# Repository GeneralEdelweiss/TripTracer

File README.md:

# TripTracer – GPS Rally & Trip Computer

Privates Entwicklungsprojekt eines selbstgebauten GPS-Tripmasters, universell fuer Rallye, Touren und Fahrzeuge. Zentraler, portabler Entwicklungsstand inklusive KiCad-10-Schaltplan, Bibliotheken, STEP-Modellen, erstem Gehaeuse und experimenteller Firmware.

## Projektstand (Oktober 2026)

| Teil | Stand | Bemerkung |
| --- | --- | --- |
| Schaltplan | V0.3 | 69 Instanzen, 25 Footprinttypen; strukturell geprueft, ERC nicht ausgefuehrt |
| Leiterplatte | Offen | **Keine geroutete, freigegebene PCB-Datei** |
| Symbole/Footprints/3D | V0.3 | Projektlokal und zentrale Kopie, Geometrie und Modelle noch zu verifizieren |
| Gehaeuse | V0.1 | Front/Rueckdeckel, Kappe, Referenzgeometrie als STEP/STL; Passprobe offen |
| Firmware | V0.1 | Experimenteller ESP32-S3-Prototyp, noch nicht mit V0.3 abgeglichen |

## Verzeichnisse

- `hardware/kicad/`: originaler V0.3-Schaltplan, projektlokale Symbole, Footprints, STEP-Modelle, Bibliothekstabellen
- `hardware/pcb/`: spaeteres Layout, momentan nur Hinweis
- `symbols/`, `footprints/`, `3dmodels/`: aus V0.3 uebernommene zentrale Bibliothekskopien
- `catalog/`: V0.3-BOM, Pin-/Netztabellen, Strukturpruefberichte, Modellinventar
- `mechanics/prototype_v0.1/`: mechanischer Prototyp (STEP/STL)
- `firmware/prototype_v0.1/`: PlatformIO-Prototyp
- `docs/HARDWARE_REQUIREMENTS.md`: zentrale Hardware-Anforderungen, Entscheidungen und offene Fragen fuer die naechste Revision
- `docs/`: Architektur, Datenblatt-URLs, Preview und offene Punkte
- `tools/legacy_generation/`: reproduzierbare Skripte der V0.3, **nicht ungefragt erneut ausfuehren**, da UUIDs neu vergeben werden koennen
- `integration/`: Bibliothekseinbindung auf weiteren Rechnern
- `releases/`: erst nach Freigabe fuellen

## Oeffnen

1. Repository klonen, KiCad 10 installieren.
2. `hardware/kicad/Tripmaster_V0_3.kicad_pro` oeffnen.
3. Bibliothekstabellen und 3D-Modelle aus demselben Ordner unveraendert belassen.
4. ERC in KiCad ausfuehren und Ergebnisse einzeln pruefen; keine PCB-Fertigungsdateien aus diesem Stand ableiten.
5. Hinweise in `docs/OPEN_ITEMS.md` beachten.

## Sicherheit und Revisionshinweise

- Es gibt **keine nachgewiesene Freigabe fuer Fahrzeugbetrieb** (Load Dump/EMV/ESD/Verpolung).
- In V0.3 ist USB-C ein selbstversorgter Datenanschluss; die Elektronik muss zum Flashen zusaetzlich ueber J1 versorgt werden.
- V0.1-Mechanik und -Firmware haben andere Revisionsnummern als V0.3 und sind nicht automatisch kompatibel.
- Keine fruehen Platzhalterfootprints aus V0.1/V0.2 als freigegebenen Produktionsstand nutzen.

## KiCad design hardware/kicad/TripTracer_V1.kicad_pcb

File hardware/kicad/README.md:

**Aktueller Eingangsschutz (14.10.2026):** [01I LM74800-Q1 (WIP)](01I_LM74800_INPUT.kicad_sch) ist im Root-KiCad-Projekt aktiv; [Bericht](../../docs/LM74800_01I_INTEGRATION_2026-10-14.md). Alte 01G-Schaltung nur Referenz. Keine PCB-/Fahrzeugfreigabe.

# TripTracer - KiCad10

Oeffne **[TripTracer_V1.kicad_pro](TripTracer_V1.kicad_pro)**. Die Rootdatei `TripTracer_V1.kicad_sch` und der Hierarchie-Navigator erschliessen alle **12 aktiven Seiten** in einem Editor.

Der aktuelle **Labor-Entwicklungsstand** verwendet:
- `01G_SIMPLE_INPUT`: S5MC1000V-Verpolschutz und TVS5800-58V-Klemmkandidat; Beschaffung und Fahrzeugpulspruefung offen.
- `01H_ACC_HOLD_GATE` und `01C_HOLD_TIMER`: VIN-gespeister ACC-Start, voraktivierter Timer und optisch entkoppelte MCU-Selbsthaltung.
- `02_5V_Buck`: LMR38020-Q1,5V/2A als Auslegungsziel.
- `03_3V3_USB`: TPS2116-Bordnetz/USB-Prioritaet und MCP1826S-3V3-LDO.
- `04_ESP32_USB`: GPIO21 HOLD, GPIO33 USB-Status, GPIO34 isolierte ACC-Erkennung; weitere Peripheriezuordnung offen.

Normalbereich9-30V, weiches Kaltstartziel etwa9V. Der alte Netzname `HV_PROTECTED_AFTER_EFUSE` ist eine Legacy-Schnittstelle und bedeutet **keine vorhandene eFuse**. Externe BAT-/ACC-Leitungsabsicherung bleibt erforderlich.

[Aktueller Eingangsentwurf, Berechnungen und Nachweise](../../docs/validation/2026-10-14-input-flat-clamp.md). Native KiCad10-Pruefungen laufen in Actions; Schaltplan-PDF, Netzliste, BOM und Berichte werden14Tage archiviert. Bestehende ERC-/DRC-Fehler, reale Thermik/Transienten und TestA202V sind nicht freigegeben. **Kein Fahrzeugbetrieb oder Fertigungsauftrag aus diesem Stand. Keine PCB-Aenderung in diesem Arbeitsblock.**

[TripTracer_V1_README.md](TripTracer_V1_README.md) enthaelt aeltere Zwischenstaende und ist ab dem gekennzeichneten Historienabschnitt **keine aktuelle Schaltungsbeschreibung**. Alte Mikrorelais-, LM74930- und LMR36520-Angaben ersetzen die aktuellen Anforderungen nicht. Die V0.3-Dateien bleiben historische Referenz.

## Kaufteile-Entscheid und Baugruppenstatus (14.10.2026)

[Nachvollziehbarer COTS-Entscheid samt konkreten Stop-Gates](../../docs/COTS_POWER_DECISION_GATE.md) und [maschinenlesbare Ist-Bestueckung](power_selection.json). COTS-first ist verbindlich, bedeutet aber **keinen blinden Austausch** einer bereits verschalteten Reglerstufe durch einen Wandler ohne EN oder mit engerer Spannungsgrenze. Die aktuell verkabelten Daten werden in CI gegen das Auswahlmanifest geprueft. **Eingangsschutz 01G bleibt entwicklungs-/beschaffungskritisch; keine Freigabe.**

### Auswahl fuer den naechsten Schutzprototypen

Der Nutzer hat LM74800-Q1 + STD17NF25 + BUK7Y4R8-60EX und zugehoerige Bauteile fixiert. Die vermeintliche 85V-Zenerdiode ist lt. TI-EVM eine 75V-Schaltdiode von A nach VS: [Entscheid samt BOM und pruefpflichtigen Punkten](../../docs/POWER_FRONTEND_DESIGN_FREEZE_2026-10-14.md), [maschinenlesbare BOM](power_frontend_design_freeze.json). **Noch nicht in der aktiven 01G_Eingangsschutz-KiCad-Schaltung verbaut.**

Die **6 zuvor offenen Standard-SMD-Positionen** der *geplanten* LM74800-BOM haben nun konkrete, beschaffbare MPNs; [DigiKey-Beschaffungscheck](../../docs/POWER_FRONTEND_PASSIVES_SOURCING_2026-10-14.md) sowie [maschinenlesbare Auswahl](power_frontend_design_freeze.json) und [CSV](power_frontend_order_bom.csv). Alle bisherigen Freigabesperren bleiben bestehen.

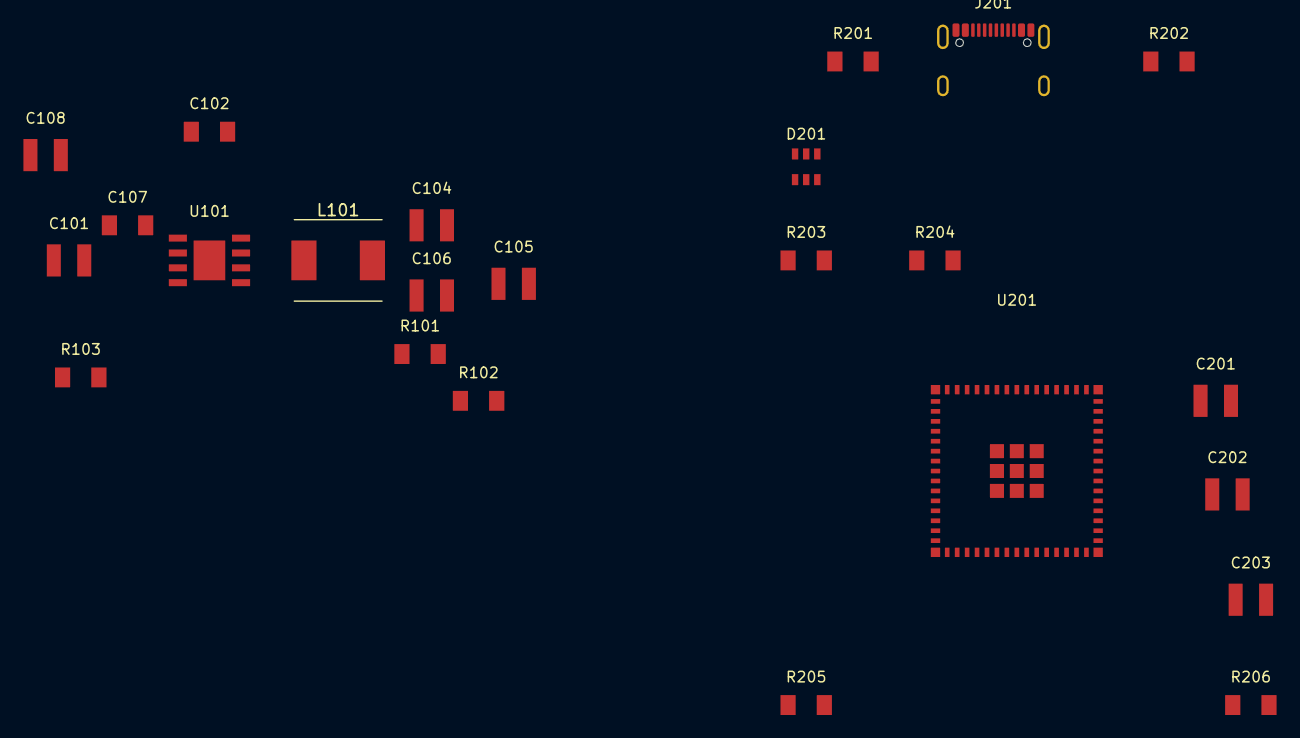
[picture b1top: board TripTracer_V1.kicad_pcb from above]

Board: 2 copper layers, 24 parts (0 on the bottom side), 19 nets, no tracks yet.

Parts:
C101, C108: 4.7uF 100V X7R VIN; C_1210_3225
C102: 100nF 100V X7R BOOT-SW; C_1206_3216
C104, C105, C106: 22uF 25V X7R VOUT; C_1210_3225
C107: 100nF 100V X7R VIN; C_1206_3216
C201: 100nF MCU local; C_1210_3225
C202: 22uF MCU bulk; C_1210_3225
C203: 1uF EN RC; C_1210_3225
D201: USBLC6-2SC6; D2_ST_USBLC6_2SC6
J201: GCT USB4105-GF-A; J1_GCT_USB4105_GF_A_USB_C
L101: 15uH FANGCHENG FCH0650-150M 5.5A Isat; L_FANGCHENG_FCH0650_150M
R101: 100k 1% FB TOP TI; R_1206_3216
R102: 24.9k 1% FB BOTTOM TI; R_1206_3216
R103: 64.9k 1% RT; R_1206_3216
R201: 5.1k CC1; R_1206_3216
R202: 5.1k CC2; R_1206_3216
R203: 22R D+; R_1206_3216
R204: 22R D-; R_1206_3216
R205: 10k BOOT PU; R_1206_3216
R206: 10k EN PU; R_1206_3216
U101: LMR38020SQDDARQ1; TI_LMR38020Q1_DDA_EP
U201: ESP32-S3-MINI-1-N8; U1_ESP32-S3-MINI-1-N8

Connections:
BOOT0_RECOVERY: R205.1, U201.4
BOOT_38020: C102.1, U101.7
EN_RESET: C203.2, R206.1, U201.45
FB_5V: R101.2, R102.1, U101.5
GND: C101.2, C104.2, C105.2, C106.2, C107.2, C108.2, C201.1, C202.1, C203.1, D201.2, J201.A1, J201.A12, J201.B1, J201.B12, J201.SH, R102.2, R103.2, R201.1, R202.2, U101.1, U101.9, U201.1, U201.2, U201.42, U201.43, U201.46, U201.47, U201.48, U201.49, U201.50, U201.51, U201.52, U201.53, U201.54, U201.55, U201.56, U201.57, U201.58, U201.59, U201.60, U201.61, U201.62, U201.63, U201.64, U201.65
HV_PROTECTED_AFTER_EFUSE: C101.1, C107.1, C108.1, U101.2, U101.3
unnamed: D201.6, R203.1
unnamed: J201.A5, R201.2
unnamed: J201.B5, R202.1
RT_400KHZ: R103.1, U101.4
SW_38020: C102.2, L101.1, U101.8
USB_DM_MCU: R204.2, U201.23
USB_DM_PORT: D201.3, J201.A7, J201.B7
USB_DM_PORT_ESD: D201.4, R204.1
USB_DP_MCU: R203.2, U201.24
USB_DP_PORT: D201.1, J201.A6, J201.B6
USB_VBUS_RAW: D201.5, J201.A4, J201.A9, J201.B4, J201.B9
V3V3_SYS: C201.2, C202.2, R205.2, R206.2, U201.3
V5_BUCK_RAW: C104.1, C105.1, C106.1, L101.2, R101.1

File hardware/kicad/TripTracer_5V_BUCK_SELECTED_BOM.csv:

Ref,Qty,Value,Manufacturer_MPN,Footprint,Source,Status
U101,1,LMR38020S-Q1 5V/2A 400kHz,LMR38020SQDDARQ1,Tripmaster:TI_LMR38020Q1_DDA_EP,https://www.ti.com/product/LMR38020-Q1,selected_not_thermally_qualified
L101,1,15uH +-20% 5A Irms 5.5A Isat,FCH0650-150M,Tripmaster:L_FANGCHENG_FCH0650_150M,https://www.lcsc.com/de/product-detail/C20415538.html,selected_footprint_geometry_UNVERIFIED
R101,1,100k 1% FB TOP,RC1206FR-07100KL,Tripmaster:R_1206_3216,https://www.yageo.com/,MPN_candidate_value_and_TCR_check_open
R102,1,24.9k 1% FB BOTTOM,RC1206FR-0724K9L,Tripmaster:R_1206_3216,https://www.yageo.com/,MPN_candidate_value_and_TCR_check_open
R103,1,64.9k 1% RT approx 400kHz,RC1206FR-0764K9L,Tripmaster:R_1206_3216,https://www.yageo.com/,MPN_candidate_frequency_tolerance_open
C101,1,4.7uF 100V X7R 1210 CIN,12101C475K4Z2A,Tripmaster:C_1210_3225,https://www.digikey.de/de/products/detail/kyocera-avx/12101C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,selected_bias_derating_unverified
C108,1,4.7uF 100V X7R 1210 CIN,12101C475K4Z2A,Tripmaster:C_1210_3225,https://www.digikey.de/de/products/detail/kyocera-avx/12101C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,selected_bias_derating_unverified
C107,1,100nF 100V X7R CIN high-frequency,C1206C104K1RACTU,Tripmaster:C_1206_3216,https://www.digikey.com/en/products/detail/kemet/C1206C104K1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,selected_position_and_parasitics_unverified
C102,1,100nF 100V X7R BOOT-to-SW,C1206C104K1RACTU,Tripmaster:C_1206_3216,https://www.digikey.com/en/products/detail/kemet/C1206C104K1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,selected
C104,1,22uF 25V X7R 1210 VOUT,GRM32ER71E226KE15L,Tripmaster:C_1210_3225,https://www.digikey.de/de/products/detail/murata-electronics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,selected_effective_C_and_transient_unverified
C105,1,22uF 25V X7R 1210 VOUT,GRM32ER71E226KE15L,Tripmaster:C_1210_3225,https://www.digikey.de/de/products/detail/murata-electronics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,selected_effective_C_and_transient_unverified
C106,1,22uF 25V X7R 1210 VOUT,GRM32ER71E226KE15L,Tripmaster:C_1210_3225,https://www.digikey.de/de/products/detail/murata-electronics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,selected_effective_C_and_transient_unverified
